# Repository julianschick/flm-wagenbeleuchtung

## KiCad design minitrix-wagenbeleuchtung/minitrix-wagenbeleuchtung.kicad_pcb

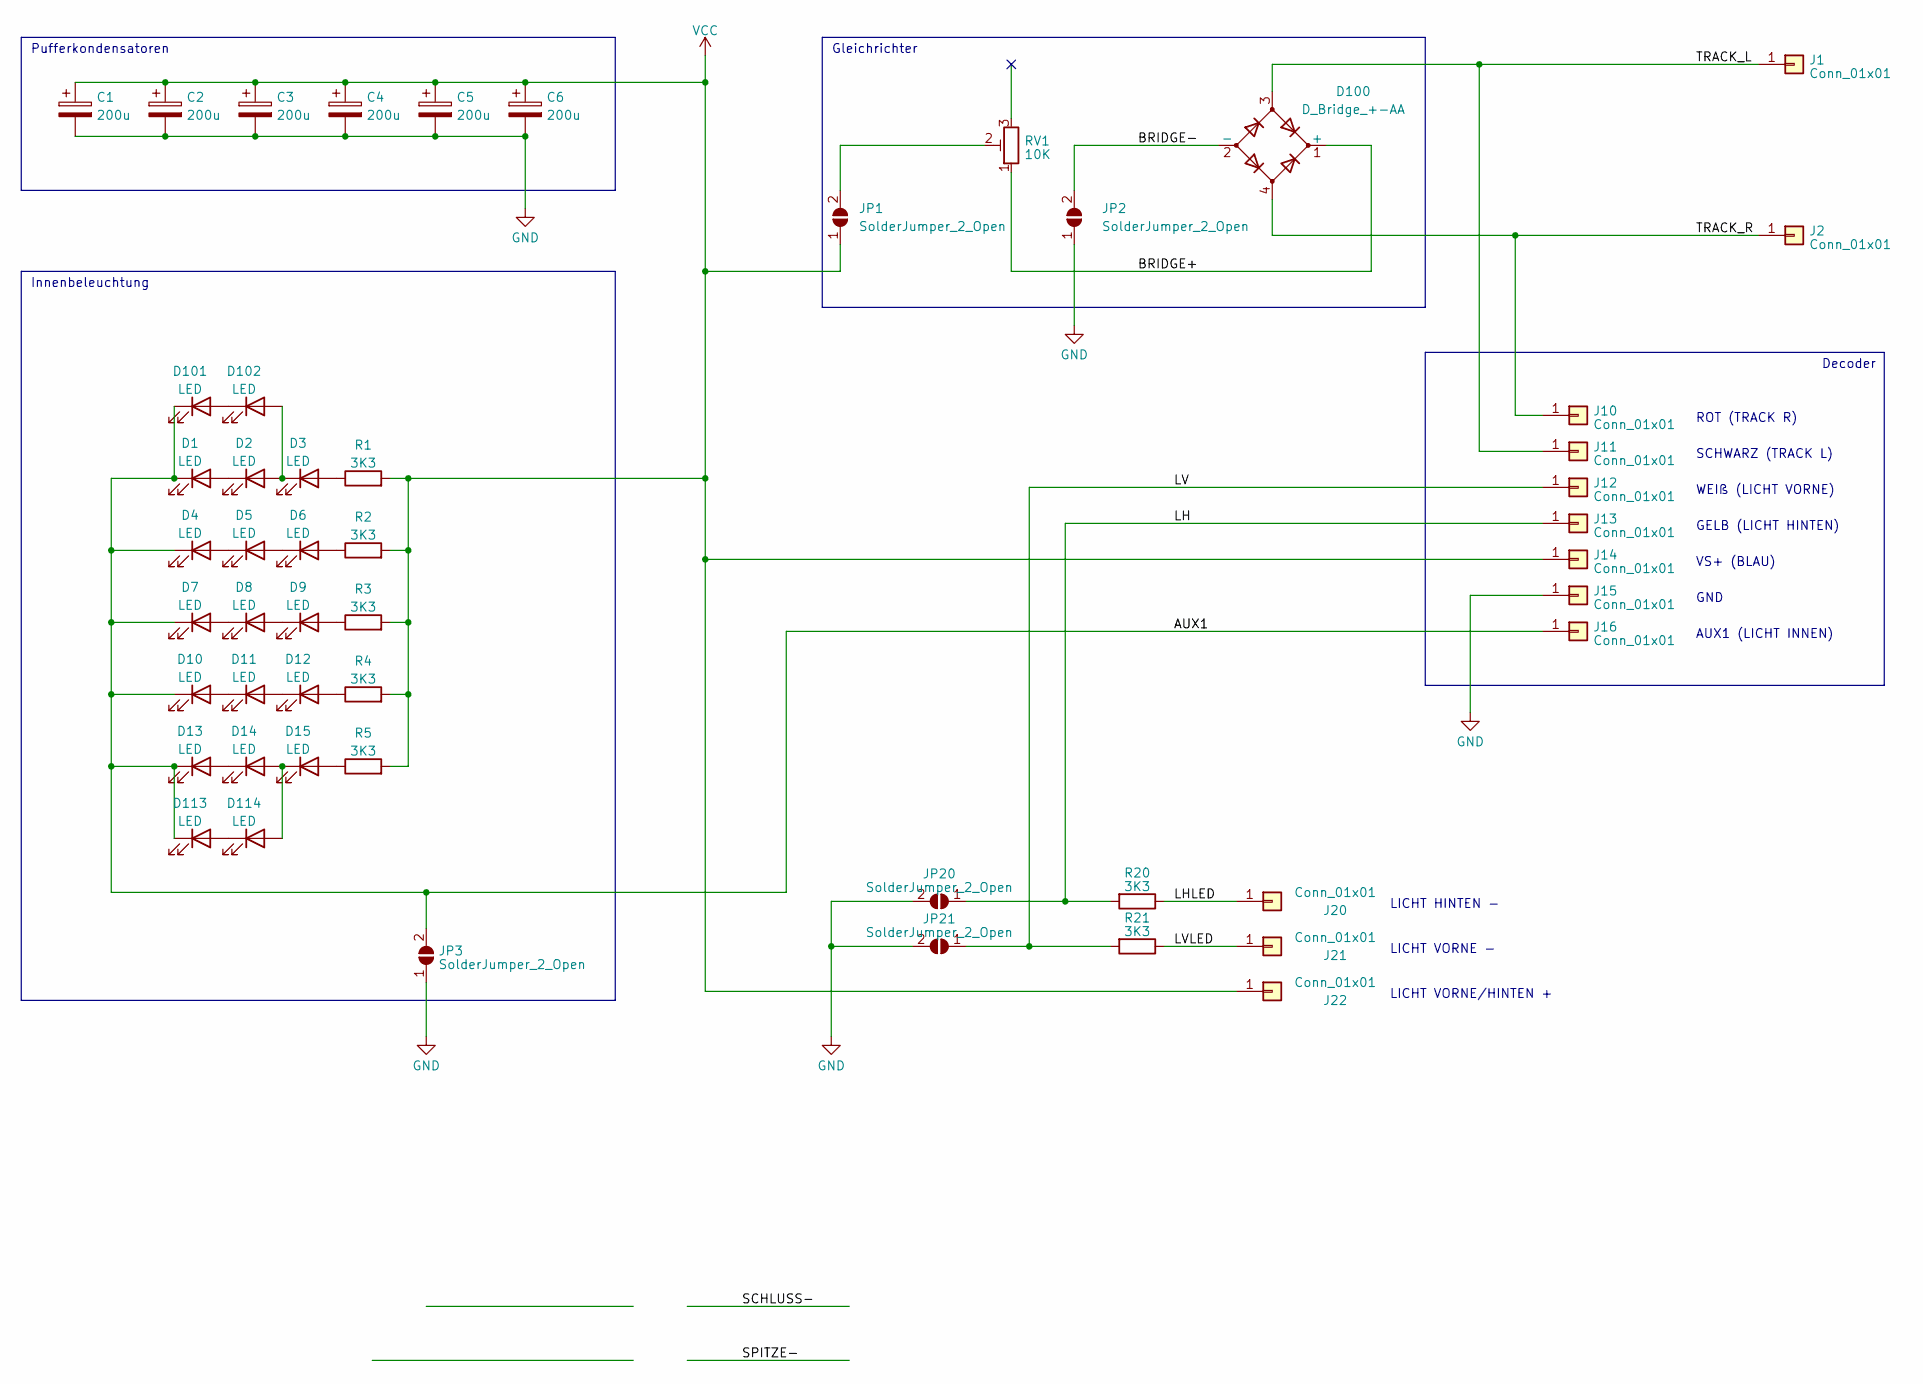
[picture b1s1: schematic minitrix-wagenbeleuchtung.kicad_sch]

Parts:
C1, C2, C3, C4, C5, C6: 200u; CP_EIA-7343-31_Kemet-D_Pad2.25x2.55mm_HandSolder
D1, D2, D3, D4, D5, D6, D7, D8, D9, D10, D11, D12, D13, D14, D15, D101, D102, D113, D114: LED; LED_PLCC_2835_Handsoldering
D100: D_Bridge_+-AA; TO-269AA
J1, J2: Conn_01x01; Minitrix_Pad
J10, J11, J12, J13, J14, J15, J16: Conn_01x01; TestPoint_Pad_1.5x1.5mm
J20, J21, J22: Conn_01x01; SolderWirePad_1x01_SMD_1x2mm
JP1, JP2, JP3, JP20, JP21: SolderJumper_2_Open; SolderJumper-2_P1.3mm_Open_RoundedPad1.0x1.5mm
R1, R2, R3, R4, R5, R20, R21: 3K3; R_1206_3216Metric_Pad1.30x1.75mm_HandSolder
RV1: 10K; Potentiometer_Bourns_TC33X_Vertical

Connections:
/AUX1: D1.1 (K), D4.1 (K), D7.1 (K), D10.1 (K), D13.1 (K), D101.1 (K), D113.1 (K), J16.1, JP3.2 (B)
/BRIDGE+: D100.1 (+), RV1.1
/BRIDGE-: D100.2 (-), JP2.2 (B)
/LH: J13.1, JP20.1 (A), R20.2
/LHLED: J20.1, R20.1
/LV: J12.1, JP21.1 (A), R21.2
/LVLED: J21.1, R21.1
/TRACK_L: D100.3, J1.1, J11.1
/TRACK_R: D100.4, J2.1, J10.1
GND: C1.2, C2.2, C3.2, C4.2, C5.2, C6.2, J15.1, JP2.1 (A), JP3.1 (A), JP20.2 (B), JP21.2 (B)
unnamed: D1.2 (A), D2.1 (K)
unnamed: D3.2 (A), R1.1
unnamed: D4.2 (A), D5.1 (K)
unnamed: D5.2 (A), D6.1 (K)
unnamed: D6.2 (A), R2.1
unnamed: D7.2 (A), D8.1 (K)
unnamed: D8.2 (A), D9.1 (K)
unnamed: D9.2 (A), R3.1
unnamed: D10.2 (A), D11.1 (K)
unnamed: D11.2 (A), D12.1 (K)
unnamed: D12.2 (A), R4.1
unnamed: D13.2 (A), D14.1 (K)
unnamed: D15.2 (A), R5.1
unnamed: D101.2 (A), D102.1 (K)
unnamed: D2.2 (A), D3.1 (K), D102.2 (A)
unnamed: D113.2 (A), D114.1 (K)
unnamed: D14.2 (A), D15.1 (K), D114.2 (A)
unnamed: JP1.2 (B), RV1.2
VCC: C1.1, C2.1, C3.1, C4.1, C5.1, C6.1, J14.1, J22.1, JP1.1 (A), R1.2, R2.2, R3.2, R4.2, R5.2

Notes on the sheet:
LICHT HINTEN -
Decoder
LICHT VORNE/HINTEN +
SCHWARZ (TRACK L)
WEIß (LICHT VORNE)
Innenbeleuchtung
ROT (TRACK R)
LICHT VORNE -
AUX1 (LICHT INNEN)
GELB (LICHT HINTEN)
Gleichrichter
Pufferkondensatoren
VS+ (BLAU)
GND

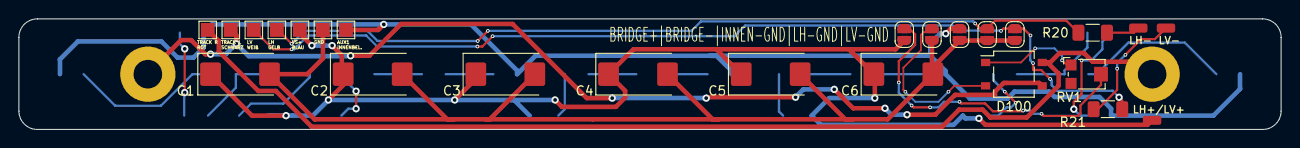
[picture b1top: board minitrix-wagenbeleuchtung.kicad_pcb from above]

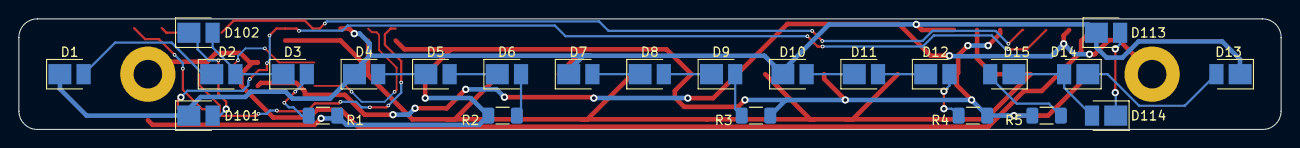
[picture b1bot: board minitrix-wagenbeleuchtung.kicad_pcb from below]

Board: 2 copper layers, 137.0 x 12.0 mm, 51 parts (26 on the bottom side), 29 nets.

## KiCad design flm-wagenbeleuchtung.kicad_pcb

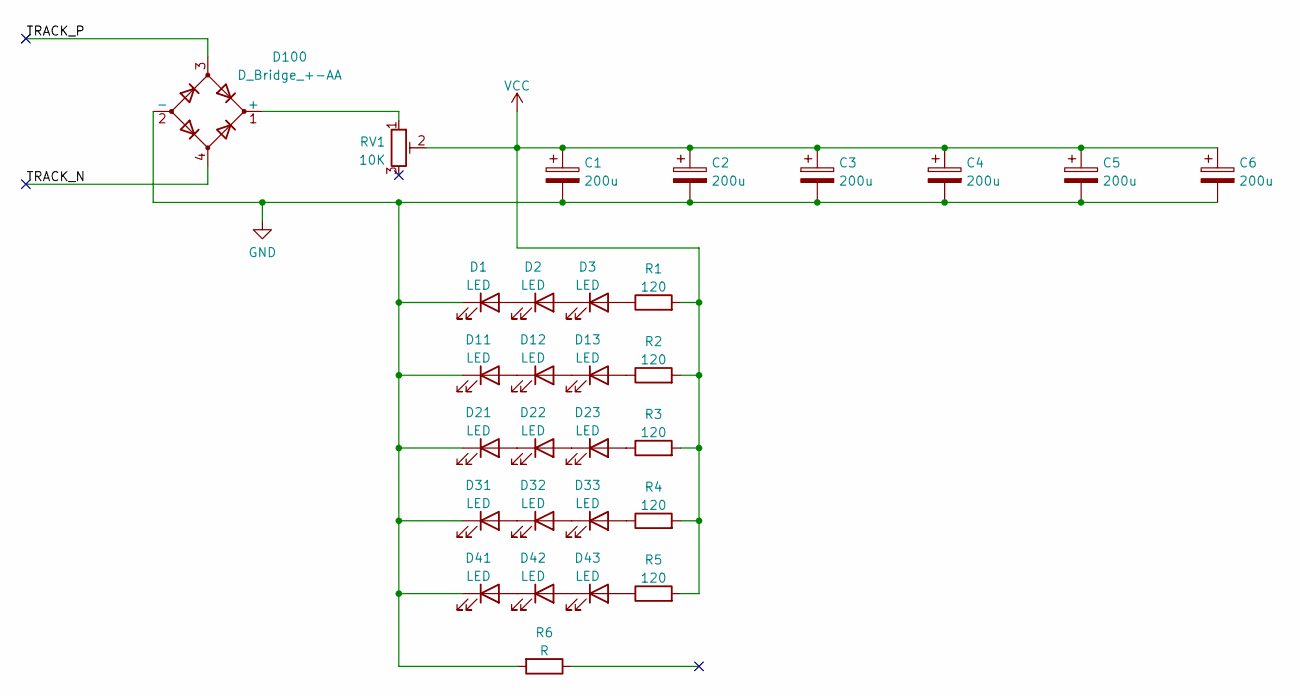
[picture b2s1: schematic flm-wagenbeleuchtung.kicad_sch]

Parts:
C1, C2, C3, C4, C5, C6: 200u; CP_EIA-7343-31_Kemet-D_Pad2.25x2.55mm_HandSolder
D1, D2, D3, D11, D12, D13, D21, D22, D23, D31, D32, D33, D41, D42, D43: LED; LED_PLCC_2835_Handsoldering
D100: D_Bridge_+-AA; TO-269AA
R1, R2, R3, R4, R5: 120; R_1206_3216Metric_Pad1.30x1.75mm_HandSolder
R6: R; R_1206_3216Metric_Pad1.30x1.75mm_HandSolder
RV1: 10K; Potentiometer_Bourns_TC33X_Vertical

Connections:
/TRACK_N: D100.4
/TRACK_P: D100.3
GND: C1.2, C2.2, C3.2, C4.2, C5.2, C6.2, D1.1 (K), D11.1 (K), D21.1 (K), D31.1 (K), D41.1 (K), D100.2 (-), R6.2
unnamed: D1.2 (A), D2.1 (K)
unnamed: D2.2 (A), D3.1 (K)
unnamed: D3.2 (A), R1.1
unnamed: D11.2 (A), D12.1 (K)
unnamed: D12.2 (A), D13.1 (K)
unnamed: D13.2 (A), R2.1
unnamed: D21.2 (A), D22.1 (K)
unnamed: D22.2 (A), D23.1 (K)
unnamed: D23.2 (A), R3.1
unnamed: D31.2 (A), D32.1 (K)
unnamed: D32.2 (A), D33.1 (K)
unnamed: D33.2 (A), R4.1
unnamed: D41.2 (A), D42.1 (K)
unnamed: D42.2 (A), D43.1 (K)
unnamed: D43.2 (A), R5.1
unnamed: D100.1 (+), RV1.1
VCC: C1.1, C2.1, C3.1, C4.1, C5.1, C6.1, R1.2, R2.2, R3.2, R4.2, R5.2, RV1.2; also elsewhere on the board

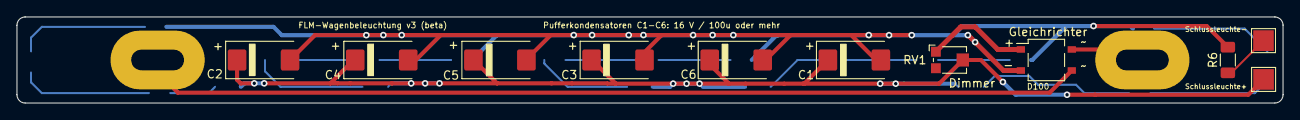
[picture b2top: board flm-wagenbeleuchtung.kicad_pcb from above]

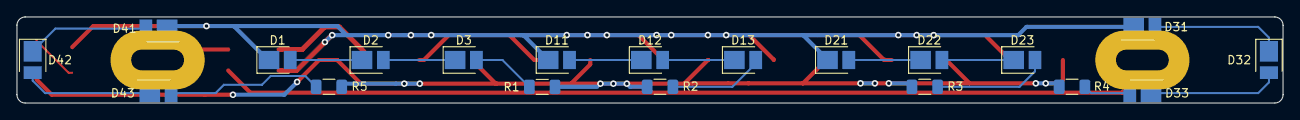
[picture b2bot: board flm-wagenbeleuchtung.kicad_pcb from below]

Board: 2 copper layers, 153.0 x 10.4 mm, 31 parts (20 on the bottom side), 18 nets.

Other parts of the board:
Schlussleuchte+: TestPoint_Pad_2.5x2.5mm
Schlussleuchte-: TestPoint_Pad_2.5x2.5mm

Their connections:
VCC: Schlussleuchte+.1; also elsewhere on the board

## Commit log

2023-01-29 initial
2023-02-15 rev1
2023-02-28 lochabstand etwas größer, damit auch restaurantwagen passen
2023-02-28 move +minitrix
2023-02-28 flm: 3k3
2023-05-05 minitrix
2023-05-15 minitrix v1
